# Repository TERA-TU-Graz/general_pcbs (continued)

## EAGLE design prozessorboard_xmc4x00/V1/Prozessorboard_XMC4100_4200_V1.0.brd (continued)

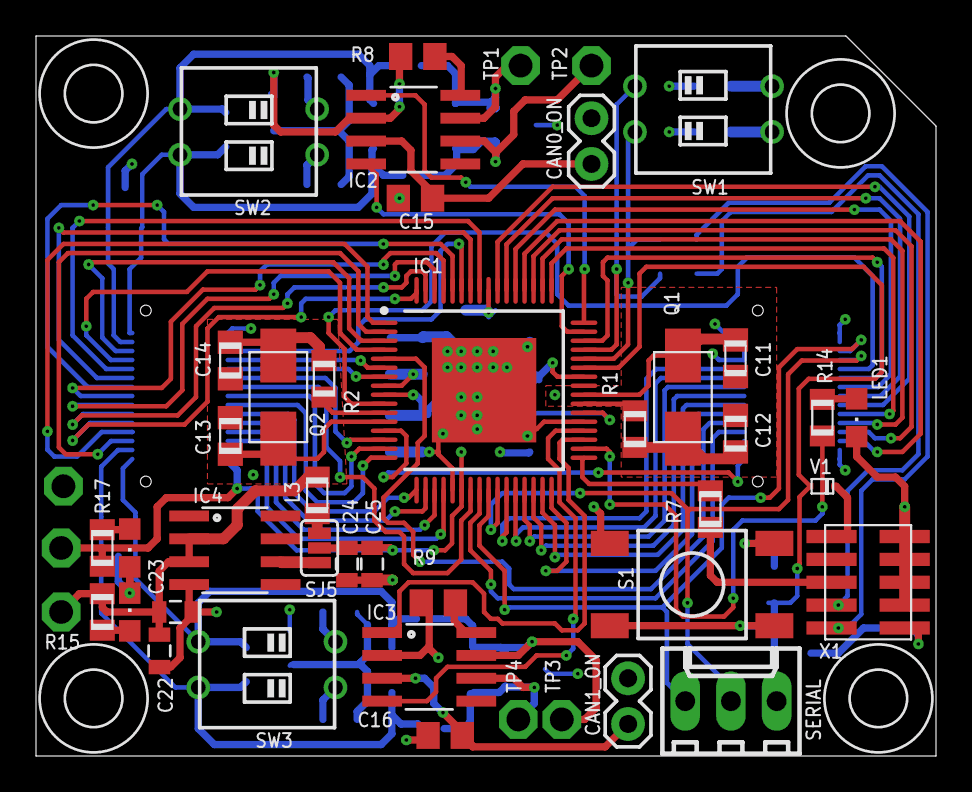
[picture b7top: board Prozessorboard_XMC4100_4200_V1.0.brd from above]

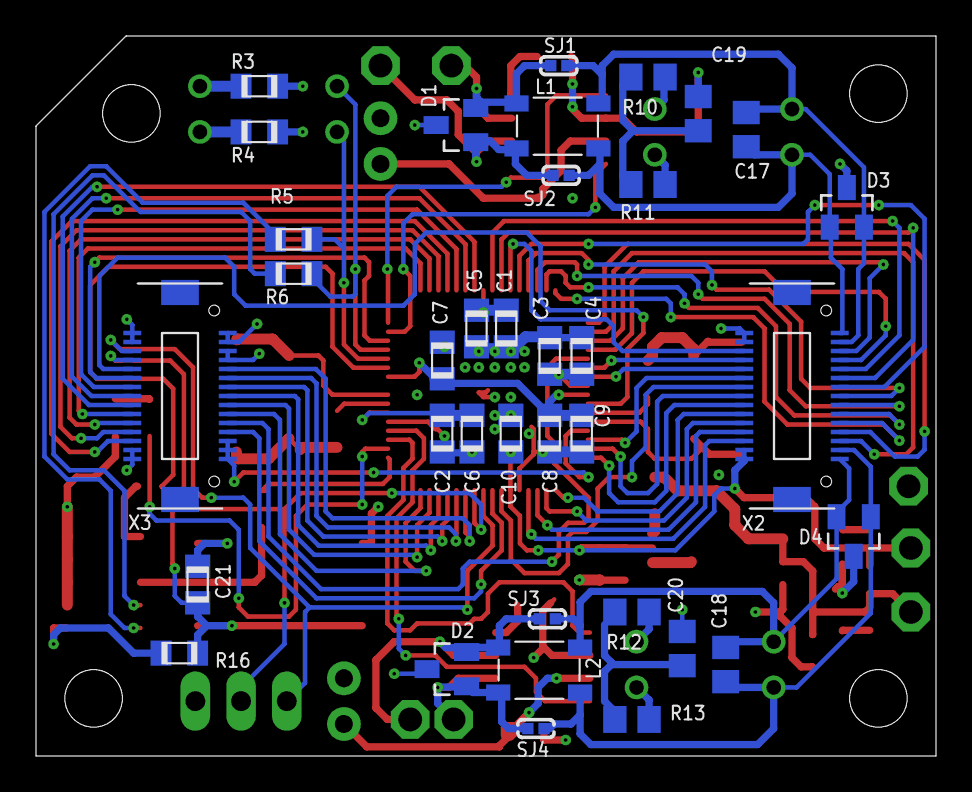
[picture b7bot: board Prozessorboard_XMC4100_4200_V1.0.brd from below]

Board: 4 copper layers, 50.0 x 40.0 mm, 85 parts (36 on the bottom side), 90 nets.
